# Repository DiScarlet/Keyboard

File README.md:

# Duck Keyboard

Why are the Space and Tab keys so big? Completely unnecessary.

We are not accountants. Why should some keys get more space than others?

We demand equality. Equality and ducks.

**52 keys. Zero keycap inequality.**

Ducks, palm trees, and pure summer vibes. Tactile. Compact.

And yes — it quacks when you press it.

Built for minimalists who still want to have fun.

## Features

* 52-key compact layout
* Uniform key sizes with no oversized Space or Tab keys
* Tactile typing experience
* Custom duck-themed design
* Compact footprint for minimalist setups
* Integrated sound effects: every keypress quacks

## Design Philosophy

Most keyboards dedicate excessive space to a handful of keys while the rest compete for room.

The Duck Keyboard rejects keycap inequality. Every key deserves equal treatment. 

## Zine

## CAD Model and Case

The keyboard case uses Gasket Mounting and was designed to complement the compact layout while maintaining a clean, minimalist appearance.

|  |  |

|  |  |

## Electronics

### Schematic

The keyboard electronics are based on a custom schematic designed usinf KiCAD.

### PCB

The custom PCB uses ESP32 Feather.

#### 3D PCB View

## Assembly Instructios
1. Flash the ESP32 Feather with the firmware.
2. Solder the hot-swap sockets and the ESP32 Feather to the PCB.
3. Install the switches into the hot-swap sockets.
4. 3D print the top case, bottom case, and keycaps.
5. Place the PCB assembly into the case and secure it using M2 screws.
6. Install the keycaps onto the switches.
7. 3D print the decorative duck and palm tree elements.
8. Attach the decorations to the designated area of the top case using instant glue (cyanoacrylate).
9. (Optional) Print the angle-of-attack wedge to tilt the keyboard toward the user for a more comfortable typing position.

## File Structure

The project layout is:

- `BoM.csv`
- `README.md`
- `CAD_Fusion/`
  - `ESP32-WROOM32-DEVBOARD_DIMENTIONS.f3d`
  - `Downloaded/`
  - `FullAssembly/`
  - `PCB/`
  - `SeparateElements/`
- `Docs/`
  - `ESP32HUZZAH32.txt`
  - `keyboard-layout.json`
  - `Links_to_parts.txt`
- `Hardware/`
  - `keyboard.kicad_sch`
  - `keyboard.kicad_pcb`
  - `keyboard.kicad_pro`
  - `keyboard.kicad_prl`
  - `keyboard-backups/`
  - `Libraries/`
- `Images/`
  - `CAD/`
  - `PCB/`
- `macropad/`
  - `Firmware/`
  - `kicad_care_package/`
  - `kicad_macropad_project/`
- `Symbols/`

## Firmware

Refer to [Firmware ReadMe](Firmware/README.md)

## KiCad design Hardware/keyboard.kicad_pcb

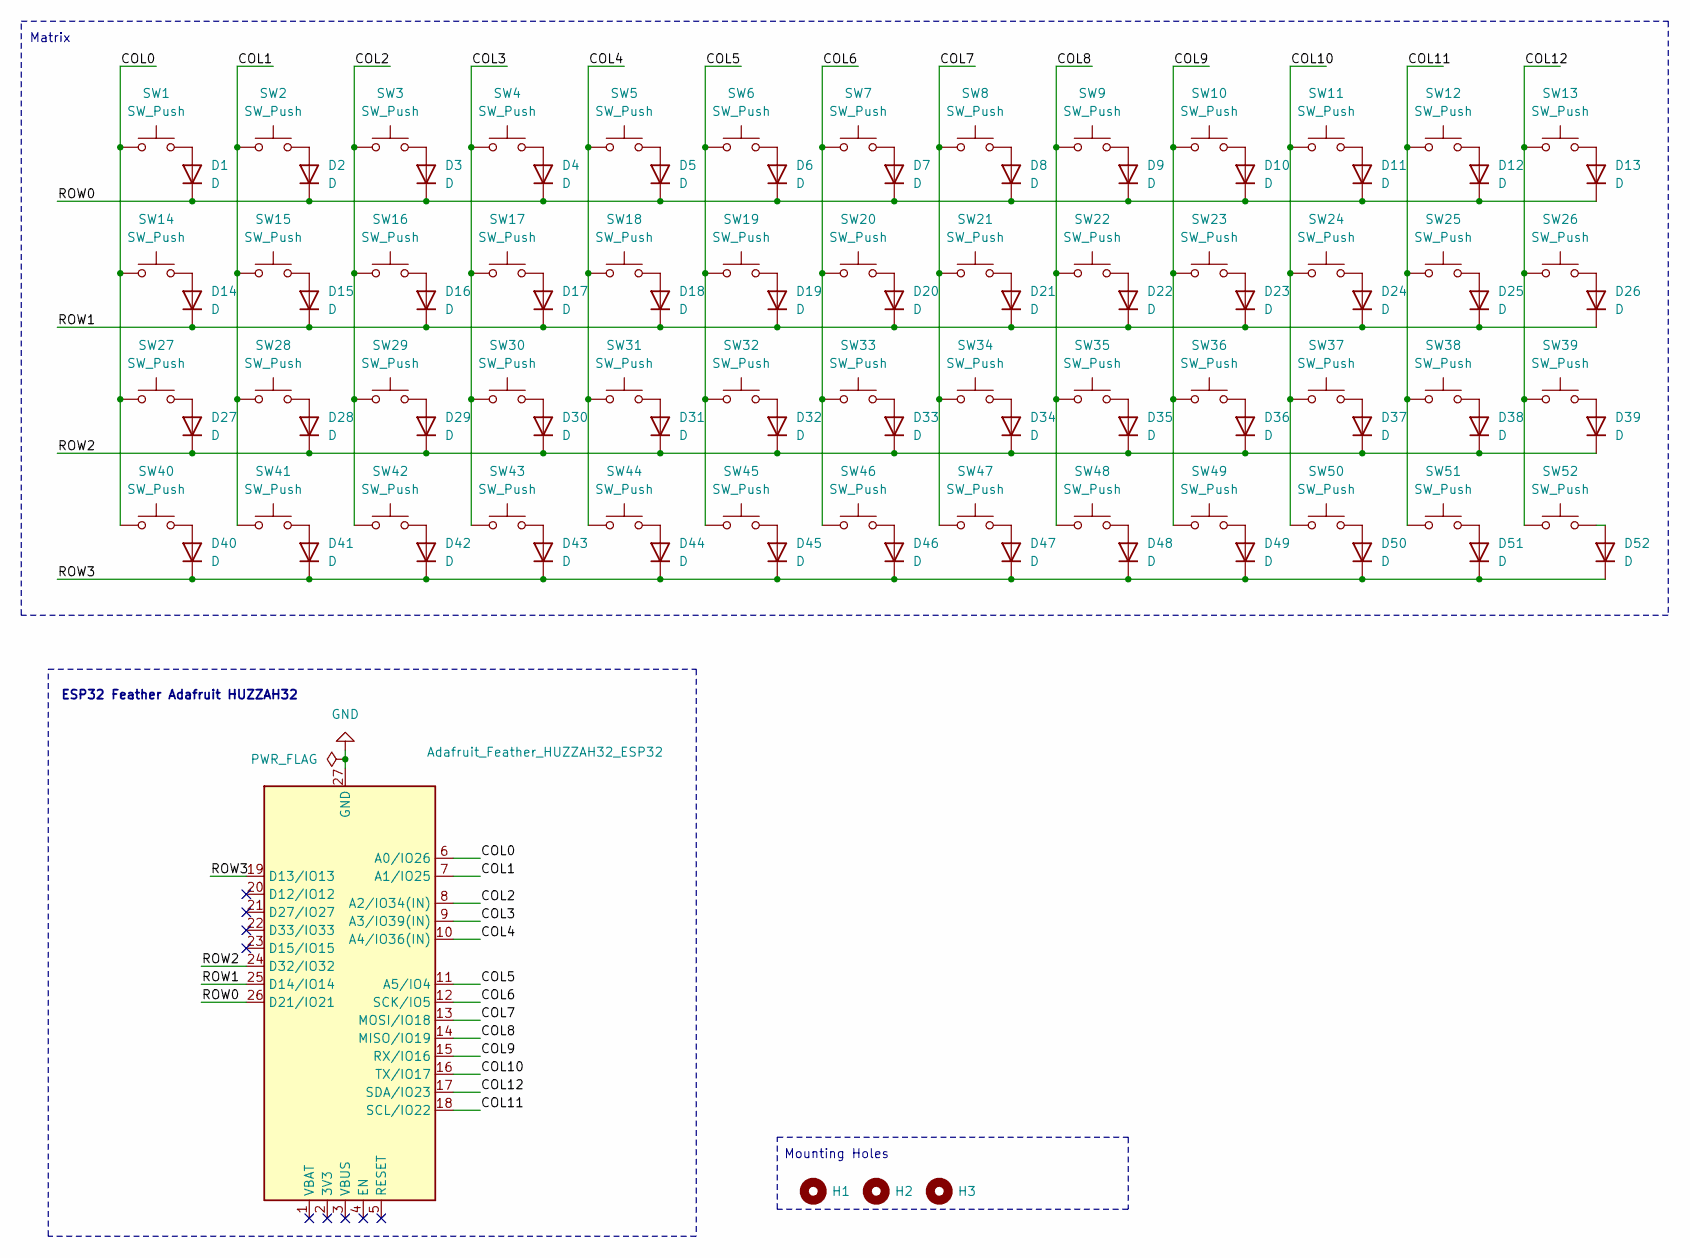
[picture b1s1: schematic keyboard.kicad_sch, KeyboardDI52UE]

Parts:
A1: Adafruit_Feather_HUZZAH32_ESP32; Adafruit_Feather
D1, D2, D3, D4, D5, D6, D7, D8, D9, D10, D11, D12, D13, D14, D15, D16, D17, D18, D19, D20, D21, D22, D23, D24, D25, D26, D27, D28, D29, D30, D31, D32, D33, D34, D35, D36, D37, D38, D39, D40, D41, D42, D43, D44, D45, D46, D47, D48, D49, D50, D51, D52: D; D_SOD-123
H1, H2, H3: MountingHole; MountingHole_2.1mm
SW1, SW2, SW3, SW4, SW5, SW6, SW7, SW8, SW9, SW10, SW11, SW12, SW13, SW14, SW15, SW16, SW17, SW18, SW19, SW20, SW21, SW22, SW23, SW24, SW25, SW26, SW27, SW28, SW29, SW30, SW31, SW32, SW33, SW34, SW35, SW36, SW37, SW38, SW39, SW40, SW41, SW42, SW43, SW44, SW45, SW46, SW47, SW48, SW49, SW50, SW51, SW52: SW_Push; SW_choc_v1_HS_CPG135001S30_1u

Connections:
/COL0: A1.6 (A0/IO26), SW1.1, SW14.1, SW27.1, SW40.1
/COL1: A1.7 (A1/IO25), SW2.1, SW15.1, SW28.1, SW41.1
/COL2: A1.8 (A2/IO34(IN)), SW3.1, SW16.1, SW29.1, SW42.1
/COL3: A1.9 (A3/IO39(IN)), SW4.1, SW17.1, SW30.1, SW43.1
/COL4: A1.10 (A4/IO36(IN)), SW5.1, SW18.1, SW31.1, SW44.1
/COL5: A1.11 (A5/IO4), SW6.1, SW19.1, SW32.1, SW45.1
/COL6: A1.12 (SCK/IO5), SW7.1, SW20.1, SW33.1, SW46.1
/COL7: A1.13 (MOSI/IO18), SW8.1, SW21.1, SW34.1, SW47.1
/COL8: A1.14 (MISO/IO19), SW9.1, SW22.1, SW35.1, SW48.1
/COL9: A1.15 (RX/IO16), SW10.1, SW23.1, SW36.1, SW49.1
/COL10: A1.16 (TX/IO17), SW11.1, SW24.1, SW37.1, SW50.1
/COL11: A1.18 (SCL/IO22), SW12.1, SW25.1, SW38.1, SW51.1
/COL12: A1.17 (SDA/IO23), SW13.1, SW26.1, SW39.1, SW52.1
/ROW0: A1.26 (D21/IO21), D1.1 (K), D2.1 (K), D3.1 (K), D4.1 (K), D5.1 (K), D6.1 (K), D7.1 (K), D8.1 (K), D9.1 (K), D10.1 (K), D11.1 (K), D12.1 (K), D13.1 (K)
/ROW1: A1.25 (D14/IO14), D14.1 (K), D15.1 (K), D16.1 (K), D17.1 (K), D18.1 (K), D19.1 (K), D20.1 (K), D21.1 (K), D22.1 (K), D23.1 (K), D24.1 (K), D25.1 (K), D26.1 (K)
/ROW2: A1.24 (D32/IO32), D27.1 (K), D28.1 (K), D29.1 (K), D30.1 (K), D31.1 (K), D32.1 (K), D33.1 (K), D34.1 (K), D35.1 (K), D36.1 (K), D37.1 (K), D38.1 (K), D39.1 (K)
/ROW3: A1.19 (D13/IO13), D40.1 (K), D41.1 (K), D42.1 (K), D43.1 (K), D44.1 (K), D45.1 (K), D46.1 (K), D47.1 (K), D48.1 (K), D49.1 (K), D50.1 (K), D51.1 (K), D52.1 (K)
GND: A1.27 (GND)
unnamed: D1.2 (A), SW1.2
unnamed: D2.2 (A), SW2.2
unnamed: D3.2 (A), SW3.2
unnamed: D4.2 (A), SW4.2
unnamed: D5.2 (A), SW5.2
unnamed: D6.2 (A), SW6.2
unnamed: D7.2 (A), SW7.2
unnamed: D8.2 (A), SW8.2
unnamed: D9.2 (A), SW9.2
unnamed: D10.2 (A), SW10.2
unnamed: D11.2 (A), SW11.2
unnamed: D12.2 (A), SW12.2
unnamed: D13.2 (A), SW13.2
unnamed: D14.2 (A), SW14.2
unnamed: D15.2 (A), SW15.2
unnamed: D16.2 (A), SW16.2
unnamed: D17.2 (A), SW17.2
unnamed: D18.2 (A), SW18.2
unnamed: D19.2 (A), SW19.2
unnamed: D20.2 (A), SW20.2
unnamed: D21.2 (A), SW21.2
unnamed: D22.2 (A), SW22.2
unnamed: D23.2 (A), SW23.2
unnamed: D24.2 (A), SW24.2
unnamed: D25.2 (A), SW25.2
unnamed: D26.2 (A), SW26.2
unnamed: D27.2 (A), SW27.2
unnamed: D28.2 (A), SW28.2
unnamed: D29.2 (A), SW29.2
unnamed: D30.2 (A), SW30.2
unnamed: D31.2 (A), SW31.2
unnamed: D32.2 (A), SW32.2
unnamed: D33.2 (A), SW33.2
unnamed: D34.2 (A), SW34.2
unnamed: D35.2 (A), SW35.2
unnamed: D36.2 (A), SW36.2
unnamed: D37.2 (A), SW37.2
unnamed: D38.2 (A), SW38.2
unnamed: D39.2 (A), SW39.2
unnamed: D40.2 (A), SW40.2
unnamed: D41.2 (A), SW41.2
unnamed: D42.2 (A), SW42.2
unnamed: D43.2 (A), SW43.2
unnamed: D44.2 (A), SW44.2
unnamed: D45.2 (A), SW45.2
unnamed: D46.2 (A), SW46.2
unnamed: D47.2 (A), SW47.2
unnamed: D48.2 (A), SW48.2
unnamed: D49.2 (A), SW49.2
unnamed: D50.2 (A), SW50.2
unnamed: D51.2 (A), SW51.2
unnamed: D52.2 (A), SW52.2

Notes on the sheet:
ESP32 Feather Adafruit HUZZAH32
Matrix
Mounting Holes

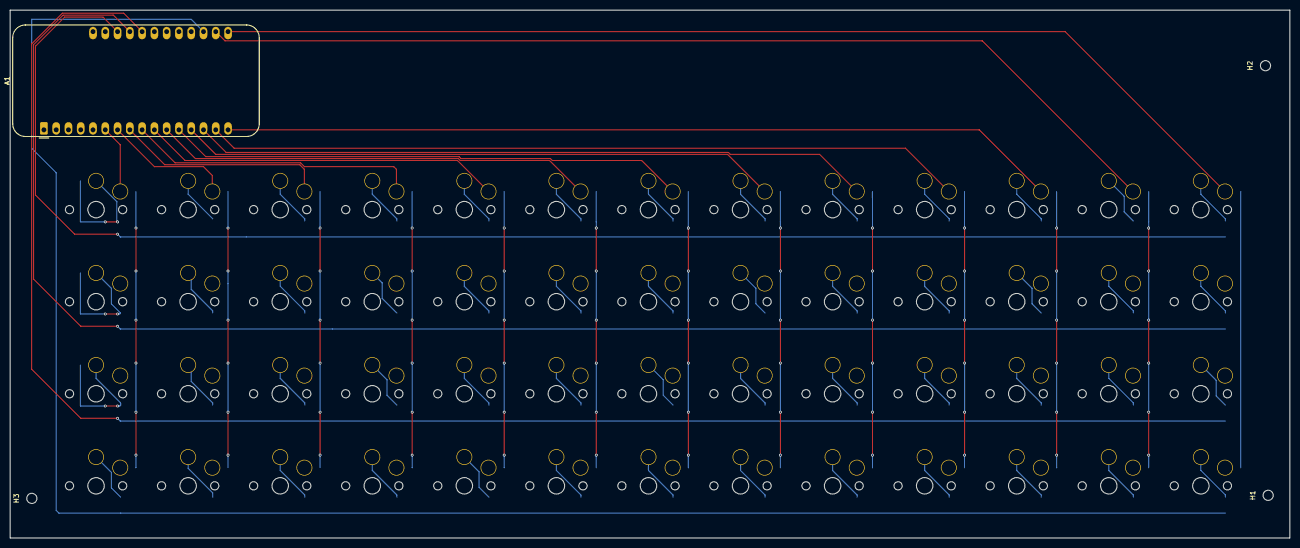
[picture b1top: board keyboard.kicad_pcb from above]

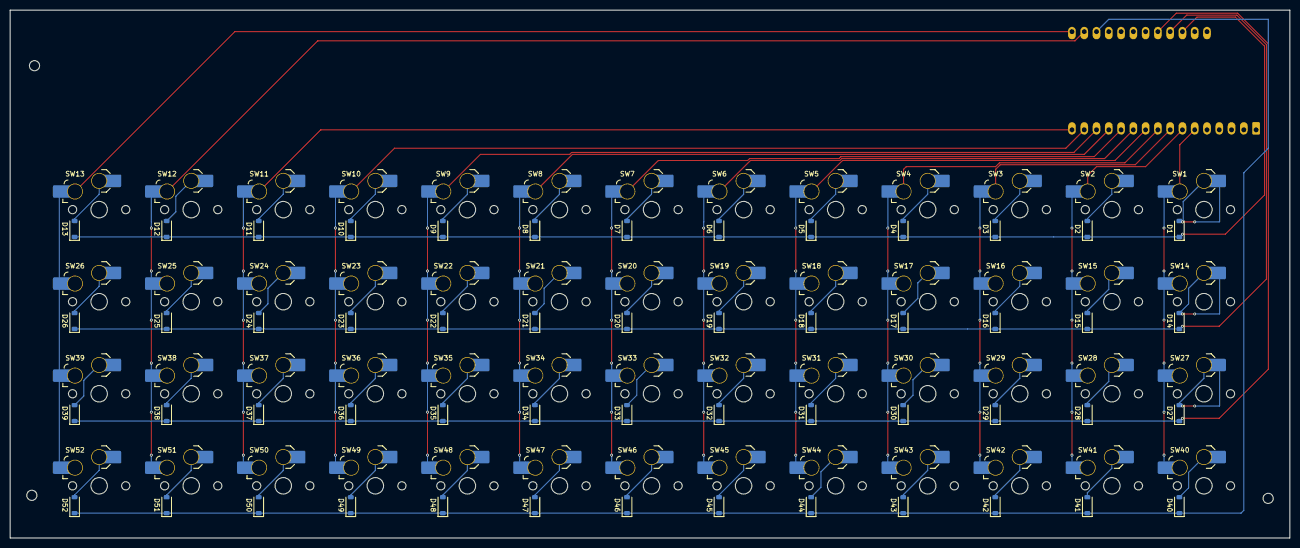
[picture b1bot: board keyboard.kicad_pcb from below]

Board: 2 copper layers, 264.8 x 109.2 mm, 108 parts (104 on the bottom side), 69 nets.

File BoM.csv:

"Reference","Value","Footprint","Datasheet","Qty","DNP","Exclude from BOM","Exclude from Board"
"A1","Adafruit_Feather_HUZZAH32_ESP32","Module:Adafruit_Feather","https://cdn-learn.adafruit.com/downloads/pdf/adafruit-huzzah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","1","","",""
"D1,D2,D3,D4,D5,D6,D7,D8,D9,D10,D11,D12,D13,D14,D15,D16,D17,D18,D19,D20,D21,D22,D23,D24,D25,D26,D27,D28,D29,D30,D31,D32,D33,D34,D35,D36,D37,D38,D39,D40,D41,D42,D43,D44,D45,D46,D47,D48,D49,D50,D51,D52","D","Diode_SMD:D_SOD-123","~","52","","",""
"H1,H2,H3,H4","MountingHole","Panelization:mouse-bite-5mm-slot","~","4","","Excluded from BOM",""
"SW1,SW2,SW3,SW4,SW5,SW6,SW7,SW8,SW9,SW10,SW11,SW12,SW13,SW14,SW15,SW16,SW17,SW18,SW19,SW20,SW21,SW22,SW23,SW24,SW25,SW26,SW27,SW28,SW29,SW30,SW31,SW32,SW33,SW34,SW35,SW36,SW37,SW38,SW39,SW40,SW41,SW42,SW43,SW44,SW45,SW46,SW47,SW48,SW49,SW50,SW51,SW52","SW_Push","PCM_marbastlib-choc:SW_choc_v1_HS_CPG135001S30_1u","~","52","","",""

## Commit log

2026-04-18 Added .gitignore
2026-04-18 Added the macropad project as the submodule
2026-04-19 Added links to parts
2026-04-19 Changed keyboard layout to 4*13
2026-04-22 Added ESP32 devboard dimentions
2026-04-22 Reorganized the repo
2026-04-22 Replaced XIAO with ESP32 devoard
2026-04-24 Swiched to ESP32 Feather Adafruit HUZZAH32
2026-04-25 Resolved ERC errors/warnings
2026-05-05 Added part 1 of PCB
2026-06-01 Added hardware source files and configure gitignore
2026-06-01 Moved ESP to the left for charging
2026-06-18 Finihed Case Design
2026-06-18 Added Zine, updated BoM
2026-06-22 Fixed model by the requirements check
